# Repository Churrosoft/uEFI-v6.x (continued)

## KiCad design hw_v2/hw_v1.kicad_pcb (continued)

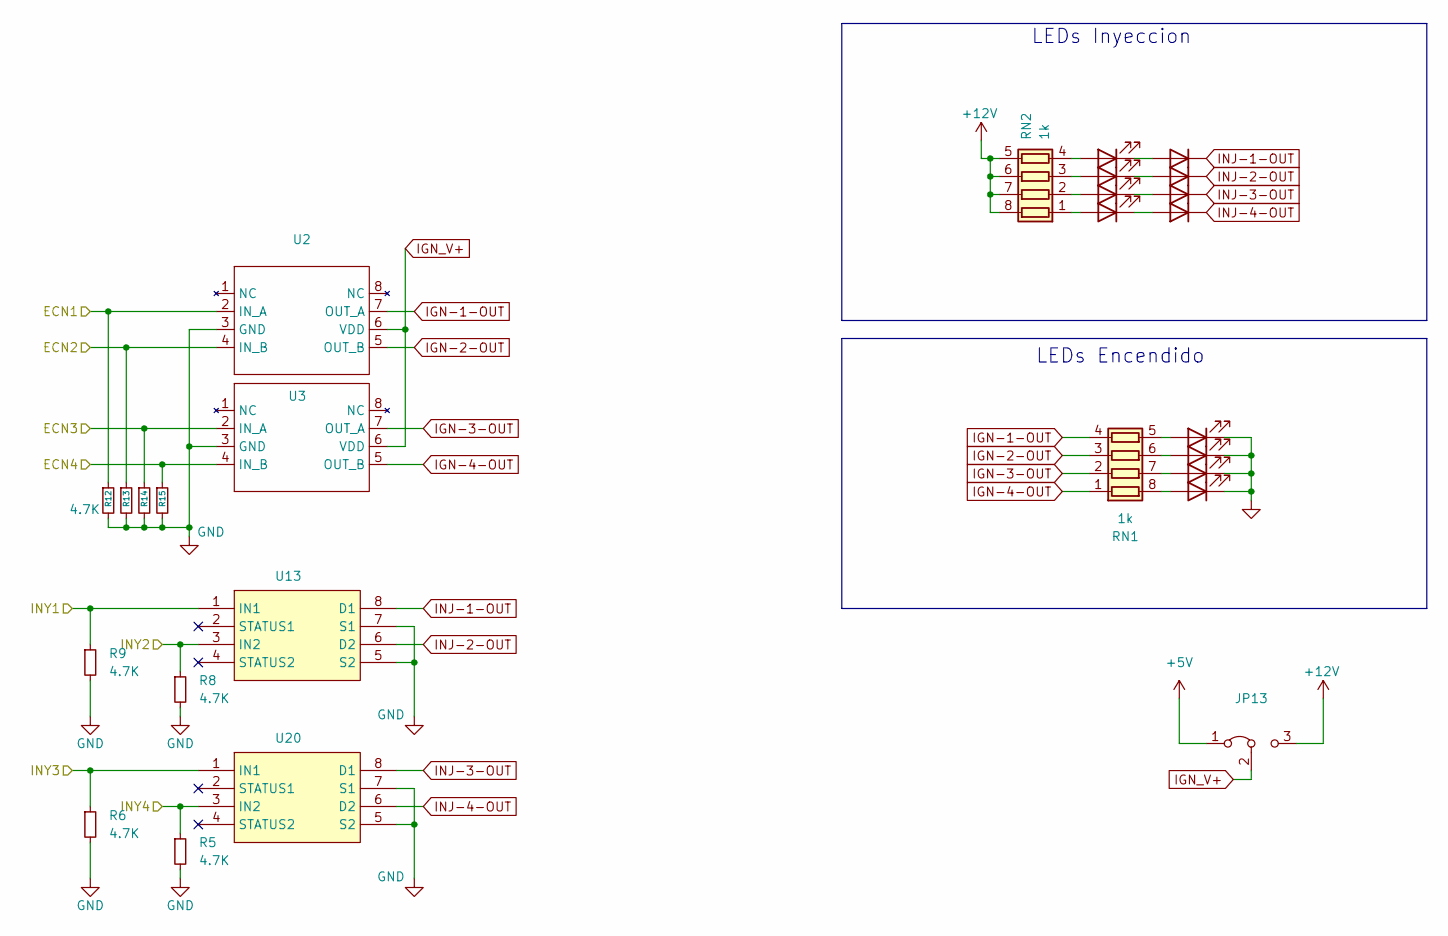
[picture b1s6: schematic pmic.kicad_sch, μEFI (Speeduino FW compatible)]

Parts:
D1, D4, D9, D12: LED; LED_0805_2012Metric; Manufacturer_Part_Number SML-H12D8TT86C; Digikey Part Number SML-H12D8TT86CCT-ND
D2, D5, D7, D10: LED; LED_0805_2012Metric; Manufacturer_Part_Number LH R974-LP-1; Digikey Part Number 475-1415-1-ND
D3, D6, D8, D11: 1N5819WS; D_SOD-323_HandSoldering; Manufacturer_Part_Number 1N4448WX-TP; LCSC C191023
JP13: Jumper_3_Bridged12; SolderJumper-3_P1.3mm_Bridged2Bar12_Pad1.0x1.5mm
R5, R6, R8, R9, R12, R13, R14, R15: 4.7K; R_0603_1608Metric; LCSC C23162
RN1, RN2: 1k; R_Array_Convex_4x0603; LCSC C110021
U2, U3: SOIC-8_3.9x4.9mm_P1.27mm; LCSC C44150
U13, U20: SO-8_3.9x4.9mm_P1.27mm; LCSC C377942

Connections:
+5V: JP13.1 (A); also elsewhere on the board
/ECN1: R13.1, U2.4 (IN_B); also elsewhere on the board
/ECN2: R12.1, U2.2 (IN_A); also elsewhere on the board
/ECN3: R15.1, U3.4 (IN_B); also elsewhere on the board
/ECN4: R14.1, U3.2 (IN_A); also elsewhere on the board
/INY1: R9.1, U13.1 (IN1); also elsewhere on the board
/INY2: R8.1, U13.3 (IN2); also elsewhere on the board
/INY3: R6.1, U20.1 (IN1); also elsewhere on the board
/INY4: R5.1, U20.3 (IN2); also elsewhere on the board
GND: D1.1 (K), D4.1 (K), D9.1 (K), D12.1 (K), R5.2, R6.2, R8.2, R9.2, R12.2, R13.2, R14.2, R15.2, U2.3 (GND), U3.3 (GND), U13.5 (S2), U13.7 (S1), U20.5 (S2), U20.7 (S1); also elsewhere on the board
HEATER+: JP13.3 (B), RN2.5 (R4.2), RN2.6 (R3.2), RN2.7 (R2.2), RN2.8 (R1.2); also elsewhere on the board
IGN-1-OUT: RN1.4 (R4.1), U2.7 (OUT_A); also elsewhere on the board
IGN-2-OUT: RN1.3 (R3.1), U2.5 (OUT_B); also elsewhere on the board
IGN-3-OUT: RN1.2 (R2.1), U3.7 (OUT_A); also elsewhere on the board
IGN-4-OUT: RN1.1 (R1.1), U3.5 (OUT_B); also elsewhere on the board
IGN_V+: JP13.2 (C), U2.6 (VDD), U3.6 (VDD)
INJ-1-OUT: D11.1 (K), U13.8 (D1); also elsewhere on the board
INJ-2-OUT: D8.1 (K), U13.6 (D2); also elsewhere on the board
INJ-3-OUT: D6.1 (K), U20.8 (D1); also elsewhere on the board
INJ-4-OUT: D3.1 (K), U20.6 (D2); also elsewhere on the board
unnamed: D1.2 (A), RN1.8 (R1.2)
unnamed: D2.2 (A), RN2.1 (R1.1)
unnamed: D2.1 (K), D3.2 (A)
unnamed: D4.2 (A), RN1.7 (R2.2)
unnamed: D5.2 (A), RN2.2 (R2.1)
unnamed: D5.1 (K), D6.2 (A)
unnamed: D7.2 (A), RN2.3 (R3.1)
unnamed: D7.1 (K), D8.2 (A)
unnamed: D9.2 (A), RN1.6 (R3.2)
unnamed: D10.2 (A), RN2.4 (R4.1)
unnamed: D10.1 (K), D11.2 (A)
unnamed: D12.2 (A), RN1.5 (R4.2)

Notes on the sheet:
LEDs Encendido
LEDs Inyeccion

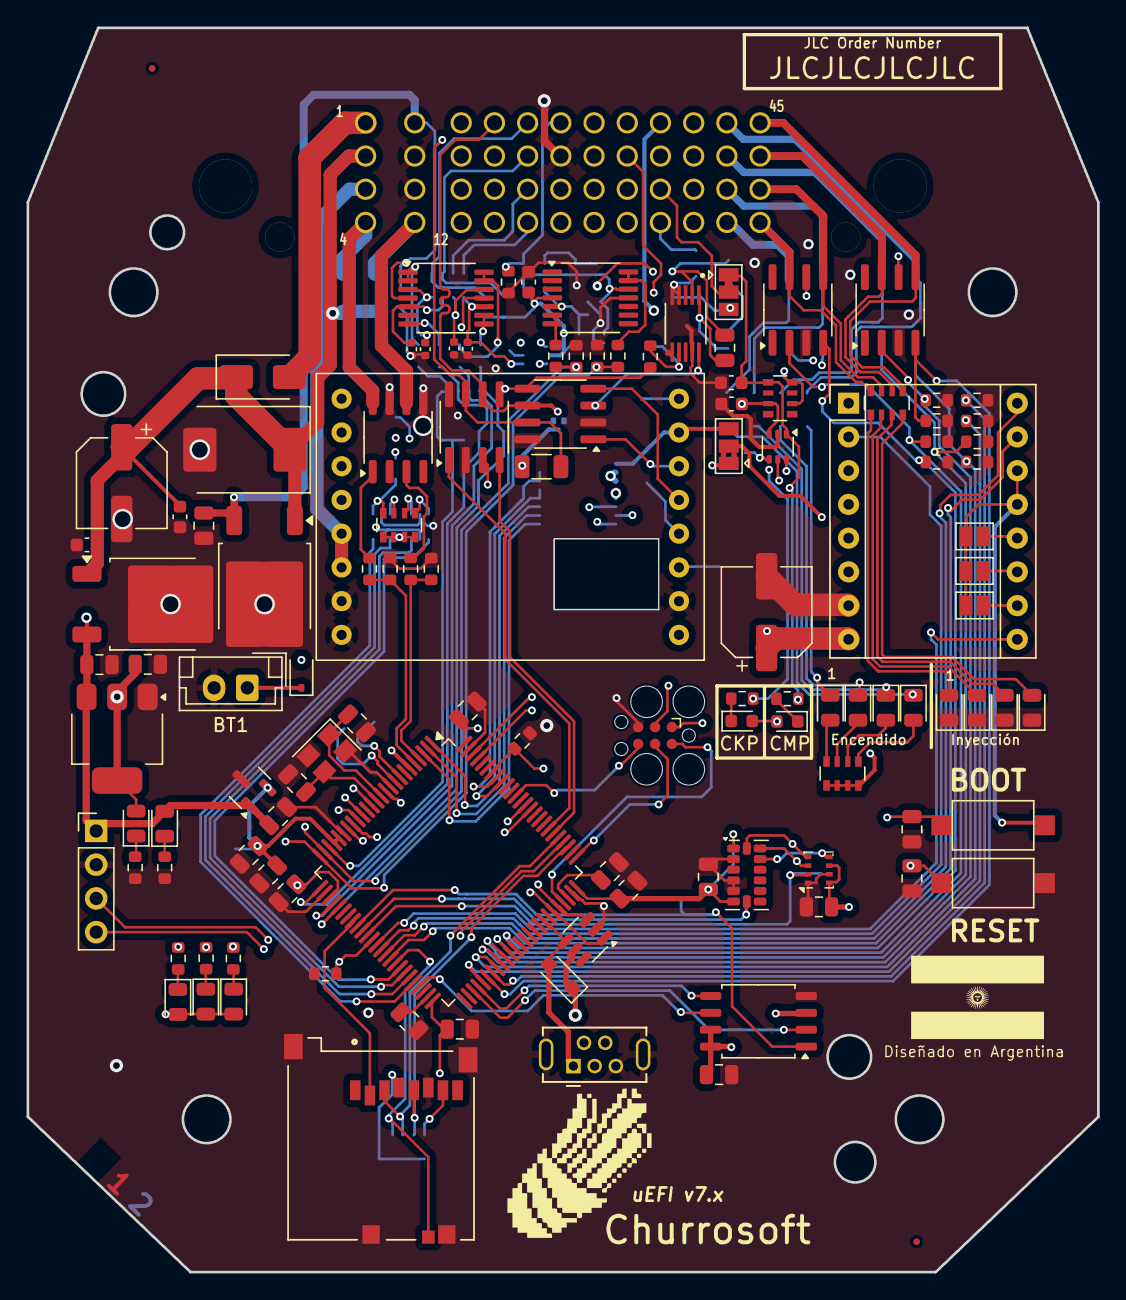
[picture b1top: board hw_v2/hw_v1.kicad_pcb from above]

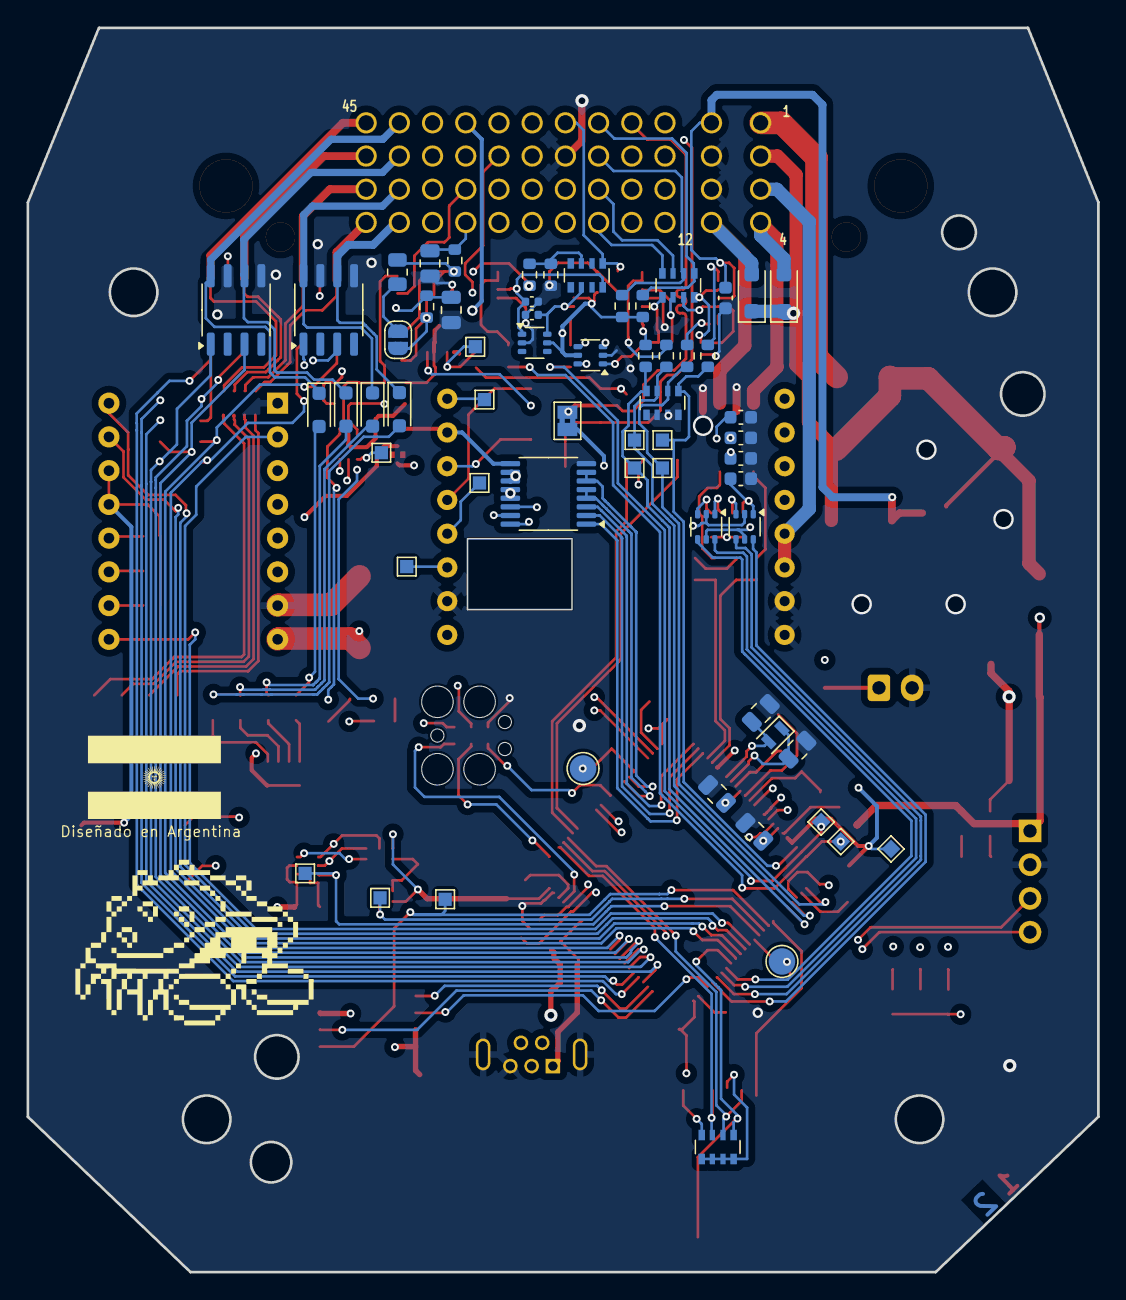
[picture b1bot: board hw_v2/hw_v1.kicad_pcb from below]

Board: 4 copper layers, 80.6 x 93.7 mm, 180 parts (61 on the bottom side), 159 nets.

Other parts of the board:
Churrosoft: SYM_Hot_Large; churro_new_v4

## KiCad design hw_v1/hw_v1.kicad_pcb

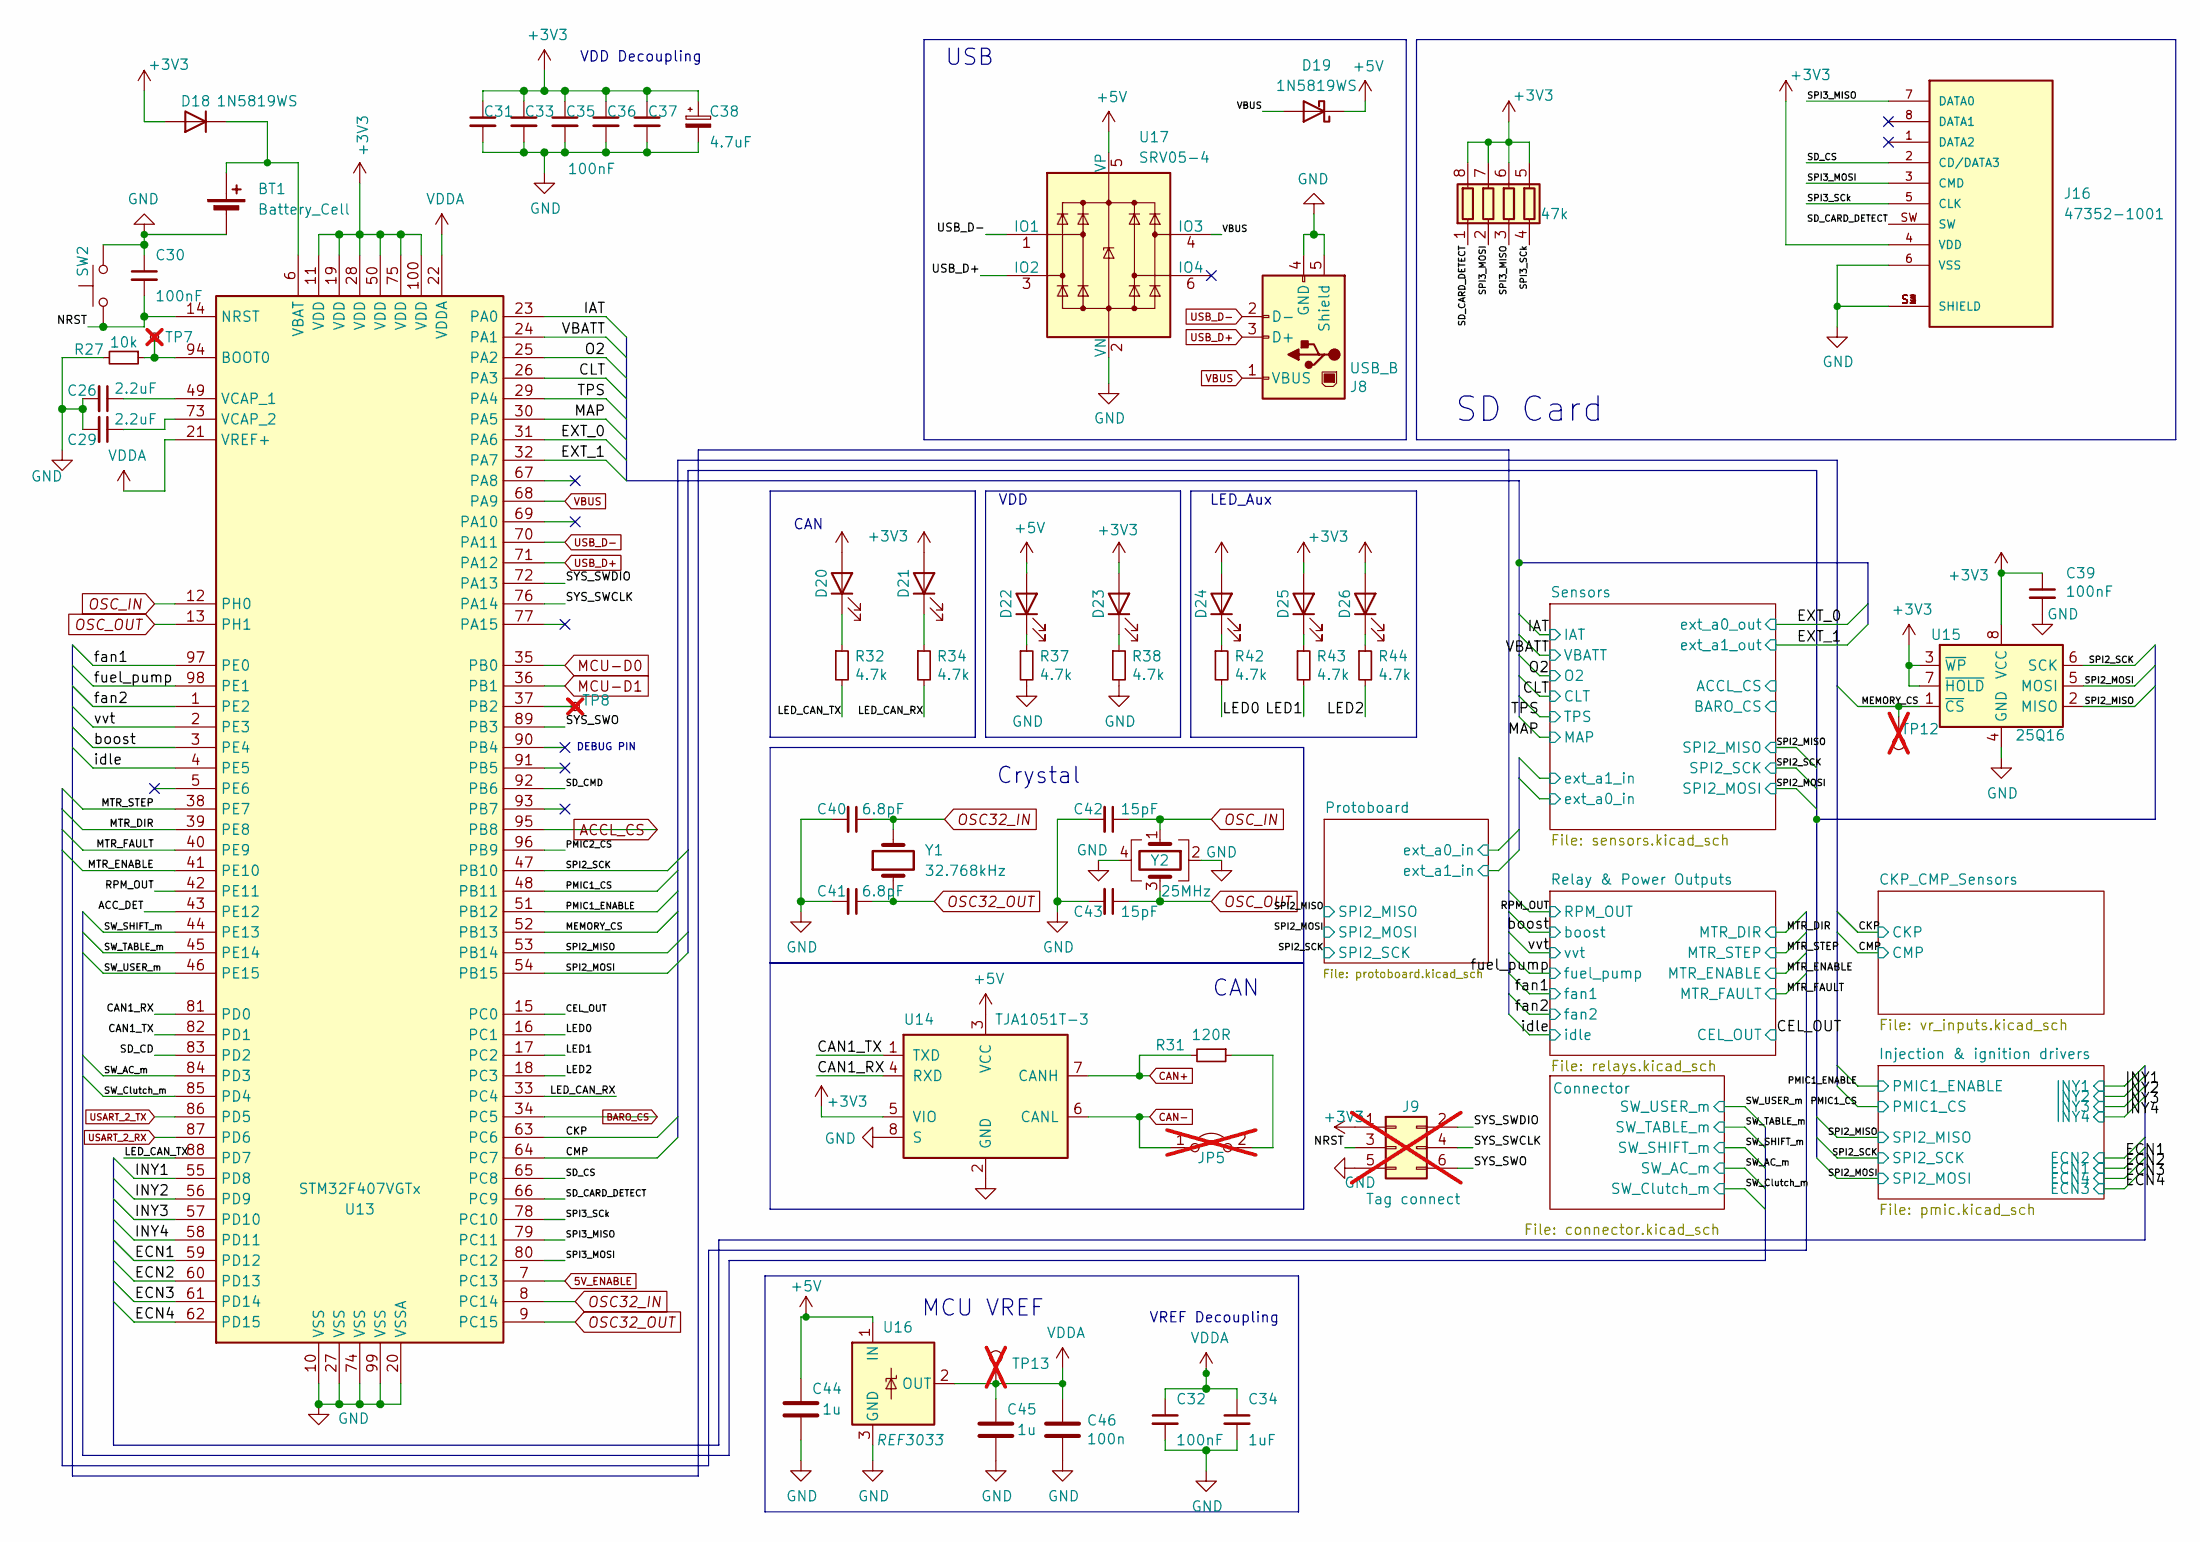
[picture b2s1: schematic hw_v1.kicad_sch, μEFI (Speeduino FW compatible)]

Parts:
BT1: Battery_Cell; JST_EH_B2B-EH-A_1x02_P2.50mm_Vertical; LCSC C722633
C26, C29: 2.2uF; C_0805_2012Metric; LCSC C377773
C30, C31, C32, C33, C35, C36, C37, C39: 100nF; C_0805_2012Metric; LCSC C49678
C34: 1uF; C_0805_2012Metric; LCSC C28323
C38: 4.7uF; C_0805_2012Metric; LCSC C1779
C40, C41: 6.8pF; C_0805_2012Metric; LCSC C282251
C42, C43: 15pF; C_0805_2012Metric; LCSC C1794
C44, C45: 1u; C_0805_2012Metric; LCSC C52923
C46: 100n; C_0805_2012Metric; LCSC C38141
D18, D19: 1N5819WS; D_SOD-323_HandSoldering; LCSC C191023
D20, D21, D22, D23, D24, D25, D26: LED; LED_0805_2012Metric; Manufacturer_Part_Number SML-H12D8TT86C; Digikey Part Number SML-H12D8TT86CCT-ND
J8: USB_B; USB_Mini-B_Tensility_54-00023_Vertical; LCSC C2682228
J9: Tag connect; Tag-Connect_TC2030-IDC-FP_2x03_P1.27mm_Vertical; not fitted
J16: 47352-1001; MOLEX_47352-1001; PARTREV K; LCSC C293569
JP5: Jumper_2_Open; SolderJumper-2_P1.3mm_Bridged2Bar_Pad1.0x1.5mm; not fitted
R27: 10k; R_0603_1608Metric; LCSC C115324
R31: 120R; R_1206_3216Metric; LCSC C144469
R32, R34, R37, R38, R42, R43, R44: 4.7k; R_0603_1608Metric; LCSC C23162
RN3: 47k; R_Array_Convex_4x0603; LCSC C779384
SW2: SW_Push; SW_SPST_TL3342; LCSC C412370
TP7: BOOT0; TestPoint_Pad_D2.0mm; not fitted
TP8: BOOT1; TestPoint_Pad_D2.0mm; not fitted
TP12, TP13: TestPoint; TestPoint_Pad_1.0x1.0mm; not fitted
U13: STM32F407VGTx; LQFP-100_14x14mm_P0.5mm; LCSC C12345
U14: TJA1051T-3; SOP-8_3.9x4.9mm_P1.27mm; LCSC C5342108
U15: 25Q16; SOIC-8_5.275x5.275mm_P1.27mm; LCSC C82317
U16: REF3033; SOT-23; LCSC C36658
U17: SRV05-4; SOT-23-6; LCSC C85364
Y1: 32.768kHz; Crystal_SMD_2012-2Pin_2.0x1.2mm; LCSC C5381473
Y2: 25MHz; Crystal_SMD_3225-4Pin_3.2x2.5mm; LCSC C9006

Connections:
5V_ENABLE: U13.7 (PC13)
+3V3: C31.1, C33.1, C35.1, C36.1, C37.1, C38.1, C39.1, D18.2 (A), D20.2 (A), D21.2 (A), D23.2 (A), D24.2 (A), D25.2 (A), D26.2 (A), J9.1, J16.4 (VDD), RN3.5 (R4.2), RN3.6 (R3.2), RN3.7 (R2.2), RN3.8 (R1.2), U13.11 (VDD), U13.19 (VDD), U13.28 (VDD), U13.50 (VDD), U13.75 (VDD), U13.100 (VDD), U14.5 (VIO), U15.3 (~WP), U15.7 (~HOLD), U15.8 (VCC); also elsewhere on the board
+5V: C44.1, D19.1 (K), D22.2 (A), U14.3 (VCC), U16.1 (IN), U17.5 (VP); also elsewhere on the board
/ACC_DET: U13.43 (PE12)
/CAN1_RX: U13.81 (PD0), U14.4 (RXD)
/CAN1_TX: U13.82 (PD1), U14.1 (TXD)
/CEL_OUT: U13.15 (PC0); also elsewhere on the board
/CKP: U13.63 (PC6); also elsewhere on the board
/CLT: U13.26 (PA3); also elsewhere on the board
/CMP: U13.64 (PC7); also elsewhere on the board
/ECN1: U13.59 (PD12); also elsewhere on the board
/ECN2: U13.60 (PD13); also elsewhere on the board
/ECN3: U13.61 (PD14); also elsewhere on the board
/ECN4: U13.62 (PD15); also elsewhere on the board
/EXT_0: U13.31 (PA6); also elsewhere on the board
/EXT_1: U13.32 (PA7); also elsewhere on the board
/IAT: U13.23 (PA0); also elsewhere on the board
/INY1: U13.55 (PD8); also elsewhere on the board
/INY2: U13.56 (PD9); also elsewhere on the board
/INY3: U13.57 (PD10); also elsewhere on the board
/INY4: U13.58 (PD11); also elsewhere on the board
/LED0: R42.2, U13.16 (PC1)
/LED1: R43.2, U13.17 (PC2)
/LED2: R44.2, U13.18 (PC3)
/LED_CAN_RX: R34.2, U13.33 (PC4)
/LED_CAN_TX: R32.2, U13.88 (PD7)
/MAP: U13.30 (PA5); also elsewhere on the board
/MEMORY_CS: TP12.1, U13.52 (PB13), U15.1 (~CS)
/MTR_DIR: U13.39 (PE8); also elsewhere on the board
/MTR_ENABLE: U13.41 (PE10); also elsewhere on the board
/MTR_FAULT: U13.40 (PE9); also elsewhere on the board
/MTR_STEP: U13.38 (PE7); also elsewhere on the board
/NRST: C30.2, J9.3, SW2.1, U13.14 (NRST)
/O2: U13.25 (PA2); also elsewhere on the board
/PMIC1_CS: U13.48 (PB11); also elsewhere on the board
/PMIC1_ENABLE: U13.51 (PB12); also elsewhere on the board
/PMIC2_CS: U13.96 (PB9)
/RPM_OUT: U13.42 (PE11); also elsewhere on the board
/SD_CARD_DETECT: J16.SW, RN3.1 (R1.1), U13.66 (PC9)
/SD_CD: U13.83 (PD2)
/SD_CMD: U13.92 (PB6)
/SD_CS: J16.2 (CD/DATA3), U13.65 (PC8)
/SPI2_MISO: U13.53 (PB14), U15.2 (MISO); also elsewhere on the board
/SPI2_MOSI: U13.54 (PB15), U15.5 (MOSI); also elsewhere on the board
/SPI2_SCK: U13.47 (PB10), U15.6 (SCK); also elsewhere on the board
/SPI3_MISO: J16.7 (DATA0), RN3.3 (R3.1), U13.79 (PC11)
/SPI3_MOSI: J16.3 (CMD), RN3.2 (R2.1), U13.80 (PC12)
/SPI3_SCk: J16.5 (CLK), RN3.4 (R4.1), U13.78 (PC10)
/SW_AC_m: U13.84 (PD3); also elsewhere on the board
/SW_Clutch_m: U13.85 (PD4); also elsewhere on the board
/SW_SHIFT_m: U13.44 (PE13); also elsewhere on the board
/SW_TABLE_m: U13.45 (PE14); also elsewhere on the board
/SW_USER_m: U13.46 (PE15); also elsewhere on the board
/SYS_SWCLK: J9.4, U13.76 (PA14)
/SYS_SWDIO: J9.2, U13.72 (PA13)
/SYS_SWO: J9.6, U13.89 (PB3)
/TPS: U13.29 (PA4); also elsewhere on the board
/VBATT: U13.24 (PA1); also elsewhere on the board
/boost: U13.3 (PE4); also elsewhere on the board
/fan1: U13.97 (PE0); also elsewhere on the board
/fan2: U13.1 (PE2); also elsewhere on the board
/fuel_pump: U13.98 (PE1); also elsewhere on the board
/idle: U13.4 (PE5); also elsewhere on the board
/vvt: U13.2 (PE3); also elsewhere on the board
ACCL_CS: U13.95 (PB8); also elsewhere on the board
BARO_CS: U13.34 (PC5); also elsewhere on the board
CAN+: R31.2, U14.7 (CANH); also elsewhere on the board
CAN-: JP5.1 (A), U14.6 (CANL); also elsewhere on the board
GND: BT1.2 (-), C26.2, C29.2, C30.1, C31.2, C32.2, C33.2, C34.2, C35.2, C36.2, C37.2, C38.2, C39.2, C40.2, C41.2, C42.2, C43.2, C44.2, C45.2, C46.2, J8.4 (GND), J8.5 (Shield), J9.5, J16.6 (VSS), J16.S1 (SHIELD), J16.S2 (SHIELD), J16.S3 (SHIELD), J16.S4 (SHIELD), R27.2, R37.2, R38.2, SW2.2, U13.10 (VSS), U13.20 (VSSA), U13.27 (VSS), U13.74 (VSS), U13.99 (VSS), U14.2 (GND), U14.8 (S), U15.4 (GND), U16.3 (GND), U17.2 (VN), Y2.2, Y2.4; also elsewhere on the board
MCU-D0: U13.35 (PB0); also elsewhere on the board
MCU-D1: U13.36 (PB1); also elsewhere on the board
unnamed: BT1.1 (+), D18.1 (K), U13.6 (VBAT)
unnamed: D20.1 (K), R32.1
unnamed: D21.1 (K), R34.1
unnamed: D22.1 (K), R37.1
unnamed: D23.1 (K), R38.1
unnamed: D24.1 (K), R42.1
unnamed: D25.1 (K), R43.1
unnamed: D26.1 (K), R44.1
unnamed: JP5.2 (B), R31.1
unnamed: R27.1, TP7.1, U13.94 (BOOT0)
unnamed: TP8.1, U13.37 (PB2)
unnamed: C26.1, U13.49 (VCAP_1)
unnamed: C29.1, U13.73 (VCAP_2)
OSC32_IN: C40.1, U13.8 (PC14), Y1.2
OSC32_OUT: C41.1, U13.9 (PC15), Y1.1
OSC_IN: C42.1, U13.12 (PH0), Y2.1
OSC_OUT: C43.1, U13.13 (PH1), Y2.3
USART_2_RX: U13.87 (PD6); also elsewhere on the board
USART_2_TX: U13.86 (PD5); also elsewhere on the board
USB_D+: J8.3 (D+), U13.71 (PA12), U17.3 (IO2)
USB_D-: J8.2 (D-), U13.70 (PA11), U17.1 (IO1)
VBUS: D19.2 (A), J8.1 (VBUS), U13.68 (PA9), U17.4 (IO3)
VDDA: C32.1, C34.1, C45.1, C46.1, TP13.1, U13.21 (VREF+), U13.22 (VDDA), U16.2 (OUT)

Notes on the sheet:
Crystal
VDD Decoupling
MCU VREF
VDD
LED_Aux
SD Card
USB
CAN
DEBUG PIN
VREF Decoupling

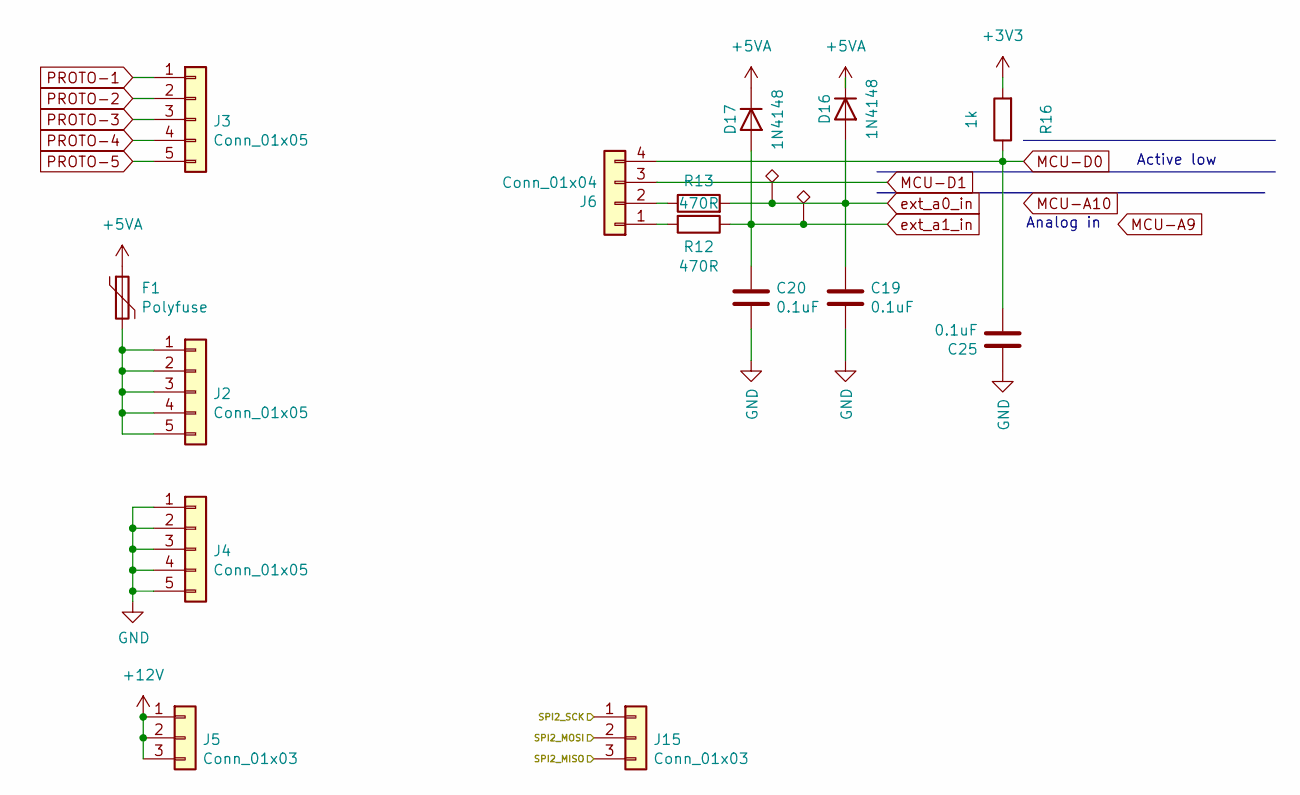
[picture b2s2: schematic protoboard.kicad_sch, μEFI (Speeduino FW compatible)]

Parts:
C19, C20, C25: 0.1uF; C_0805_2012Metric; Manufacturer_Part_Number CC0805KRX7R9BB104; Digikey Part Number 311-1140-1-ND
D16, D17: 1N4148; D_SOD-523; LCSC C5277952
F1: Polyfuse; Fuse_1812_4532Metric; Manufacturer_Part_Number 0ZCC0050FF2C; Digikey Part Number 507-1361-1-ND
J2, J3, J4: Conn_01x05; PinHeader_1x05_P2.54mm_Vertical
J5, J15: Conn_01x03; PinHeader_1x03_P2.54mm_Vertical
J6: Conn_01x04; PinHeader_1x04_P2.54mm_Vertical
R12, R13: 470R; R_0805_2012Metric; Manufacturer_Part_Number ERJ-6ENF4700V; Digikey Part Number P470CCT-ND
R16: 1k; R_0603_1608Metric; Manufacturer_Part_Number RC0805FR-071KL; Digikey Part Number 311-1.00KCRCT-ND
TP17, TP18: TestPoint_Alt; TestPoint_THTPad_1.0x1.0mm_Drill0.5mm

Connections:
+3V3: R16.2; also elsewhere on the board
+5C: D16.1 (K), D17.1 (K), F1.1; also elsewhere on the board
+12V: J5.1, J5.2, J5.3; also elsewhere on the board
/SPI2_MISO: J15.3; also elsewhere on the board
/SPI2_MOSI: J15.2; also elsewhere on the board
/SPI2_SCK: J15.1; also elsewhere on the board
CEL-OUT: J3.5; also elsewhere on the board
GND: C19.2, C20.2, C25.1, J4.1, J4.2, J4.3, J4.4, J4.5; also elsewhere on the board
MCU-D0: C25.2, J6.4, R16.1; also elsewhere on the board
MCU-D1: J6.3; also elsewhere on the board
unnamed: F1.2, J2.1, J2.2, J2.3, J2.4, J2.5
unnamed: J6.1, R13.2
unnamed: J6.2, R12.1
PROTO-1: J3.1; also elsewhere on the board
PROTO-2: J3.2; also elsewhere on the board
PROTO-3: J3.3; also elsewhere on the board
PROTO-4: J3.4; also elsewhere on the board
ext_a0_in: C19.1, D16.2 (A), R12.2, TP17.1; also elsewhere on the board
ext_a1_in: C20.1, D17.2 (A), R13.1, TP18.1; also elsewhere on the board

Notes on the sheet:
Active low
Analog in

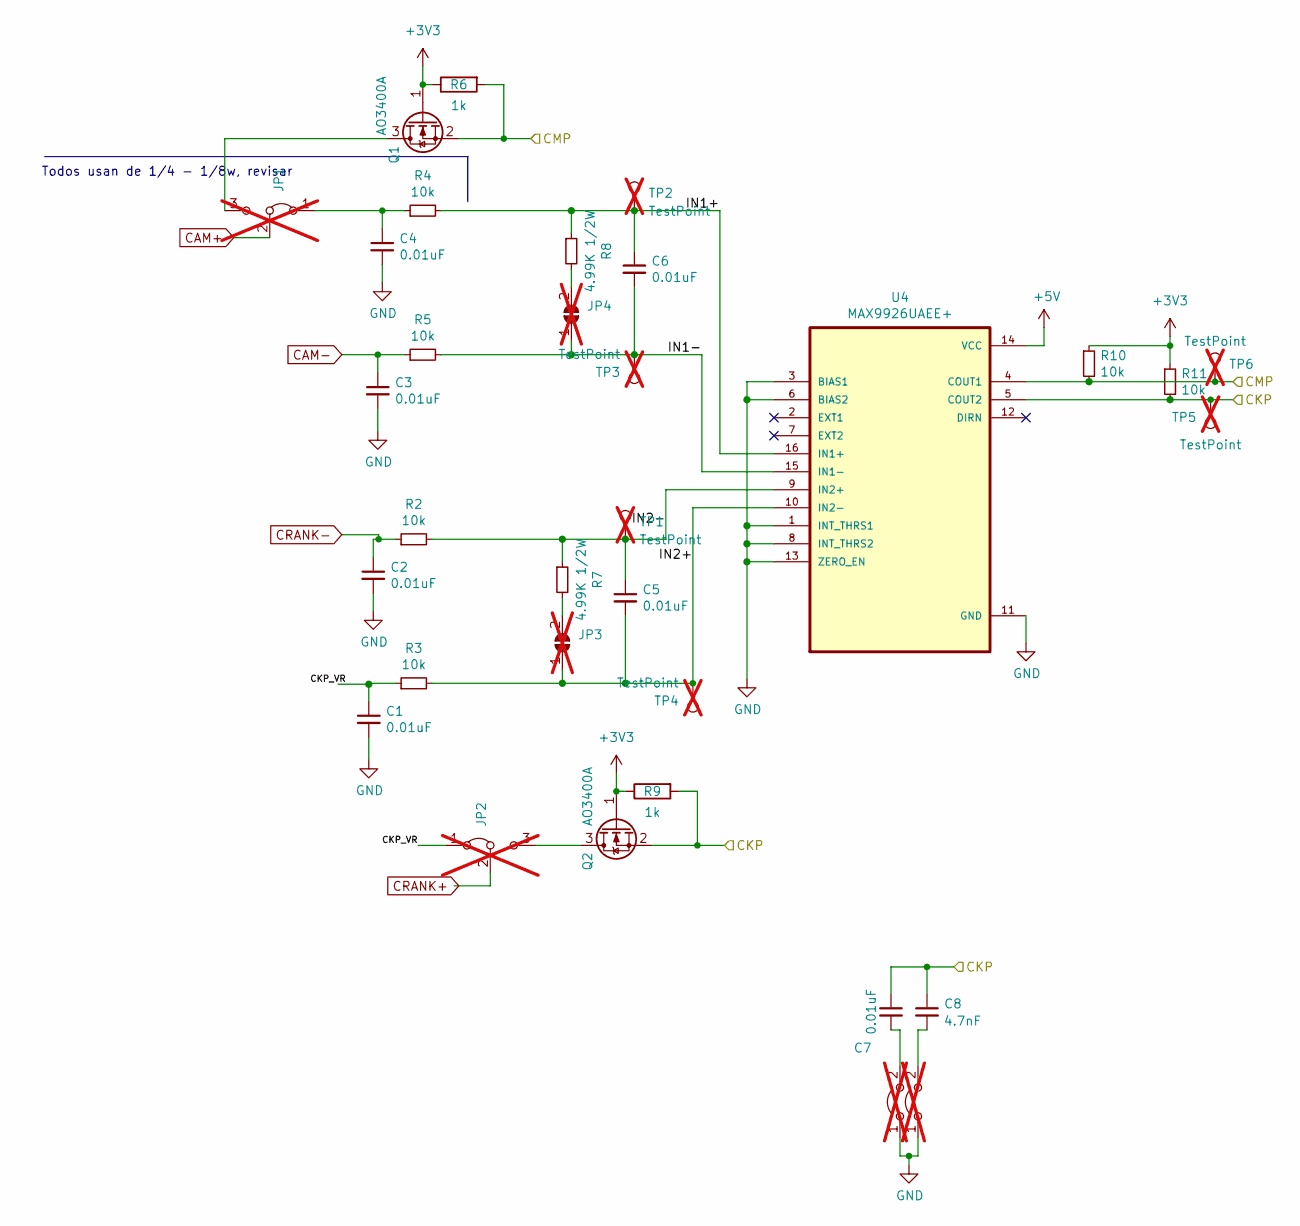
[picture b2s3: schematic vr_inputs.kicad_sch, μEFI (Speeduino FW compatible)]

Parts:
C1, C2, C3, C4, C5, C6, C7: 0.01uF; C_0805_2012Metric; LCSC C100042
C8: 4.7nF; C_0805_2012Metric; LCSC C106218
JP1, JP2: Jumper_3_Bridged12; SolderJumper-3_P1.3mm_Bridged12_Pad1.0x1.5mm; not fitted
JP3, JP4: SolderJumper_2_Open; SolderJumper-2_P1.3mm_Open_RoundedPad1.0x1.5mm; not fitted
JP11, JP12: Jumper_2_Open; SolderJumper-2_P1.3mm_Open_RoundedPad1.0x1.5mm; not fitted
Q1, Q2: AO3400A; SOT-23; LCSC C347475
R2, R3, R4, R5, R10, R11: 10k; R_0603_1608Metric; LCSC C115324
R6, R9: 1k; R_0603_1608Metric; LCSC C21190
R7, R8: 4.99K 1/2W; R_0805_2012Metric; LCSC C2933454
TP1, TP2, TP3, TP4, TP5, TP6: TestPoint; TestPoint_Pad_1.0x1.0mm; not fitted
U4: MAX9926UAEE+; QSOP-16_3.9x4.9mm_P0.635mm

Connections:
+3V3: Q1.1 (G), Q2.1 (G), R6.1, R9.1, R10.1, R11.1; also elsewhere on the board
+5V: U4.14 (VCC); also elsewhere on the board
/CKP: C7.1, C8.1, Q2.2 (S), R9.2, R11.2, TP5.1, U4.5 (COUT2); also elsewhere on the board
/CKP_CMP_Sensors/CKP_VR: C1.1, JP2.1 (A), R3.1
/CKP_CMP_Sensors/IN1+: C6.1, R4.2, R8.1, TP2.1, U4.16 (IN1+)
/CKP_CMP_Sensors/IN1-: C6.2, JP4.1 (A), R5.2, TP3.1, U4.15 (IN1-)
/CKP_CMP_Sensors/IN2+: C5.2, JP3.1 (A), R3.2, TP4.1, U4.10 (IN2-)
/CKP_CMP_Sensors/IN2-: C5.1, R2.2, R7.1, TP1.1, U4.9 (IN2+)
/CMP: Q1.2 (S), R6.2, R10.2, TP6.1, U4.4 (COUT1); also elsewhere on the board
CAM+: JP1.2 (C); also elsewhere on the board
CAM-: C3.1, R5.1; also elsewhere on the board
CRANK+: JP2.2 (C); also elsewhere on the board
CRANK-: C2.1, R2.1; also elsewhere on the board
GND: C1.2, C2.2, C3.2, C4.2, JP11.1 (A), JP12.1 (A), U4.1 (INT_THRS1), U4.3 (BIAS1), U4.6 (BIAS2), U4.8 (INT_THRS2), U4.11 (GND), U4.13 (ZERO_EN); also elsewhere on the board
unnamed: C4.1, JP1.1 (A), R4.1
unnamed: JP1.3 (B), Q1.3 (D)
unnamed: JP2.3 (B), Q2.3 (D)
unnamed: JP3.2 (B), R7.2
unnamed: JP4.2 (B), R8.2
unnamed: C7.2, JP11.2 (B)
unnamed: C8.2, JP12.2 (B)

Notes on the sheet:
Todos usan de 1/4 - 1/8w, revisar
